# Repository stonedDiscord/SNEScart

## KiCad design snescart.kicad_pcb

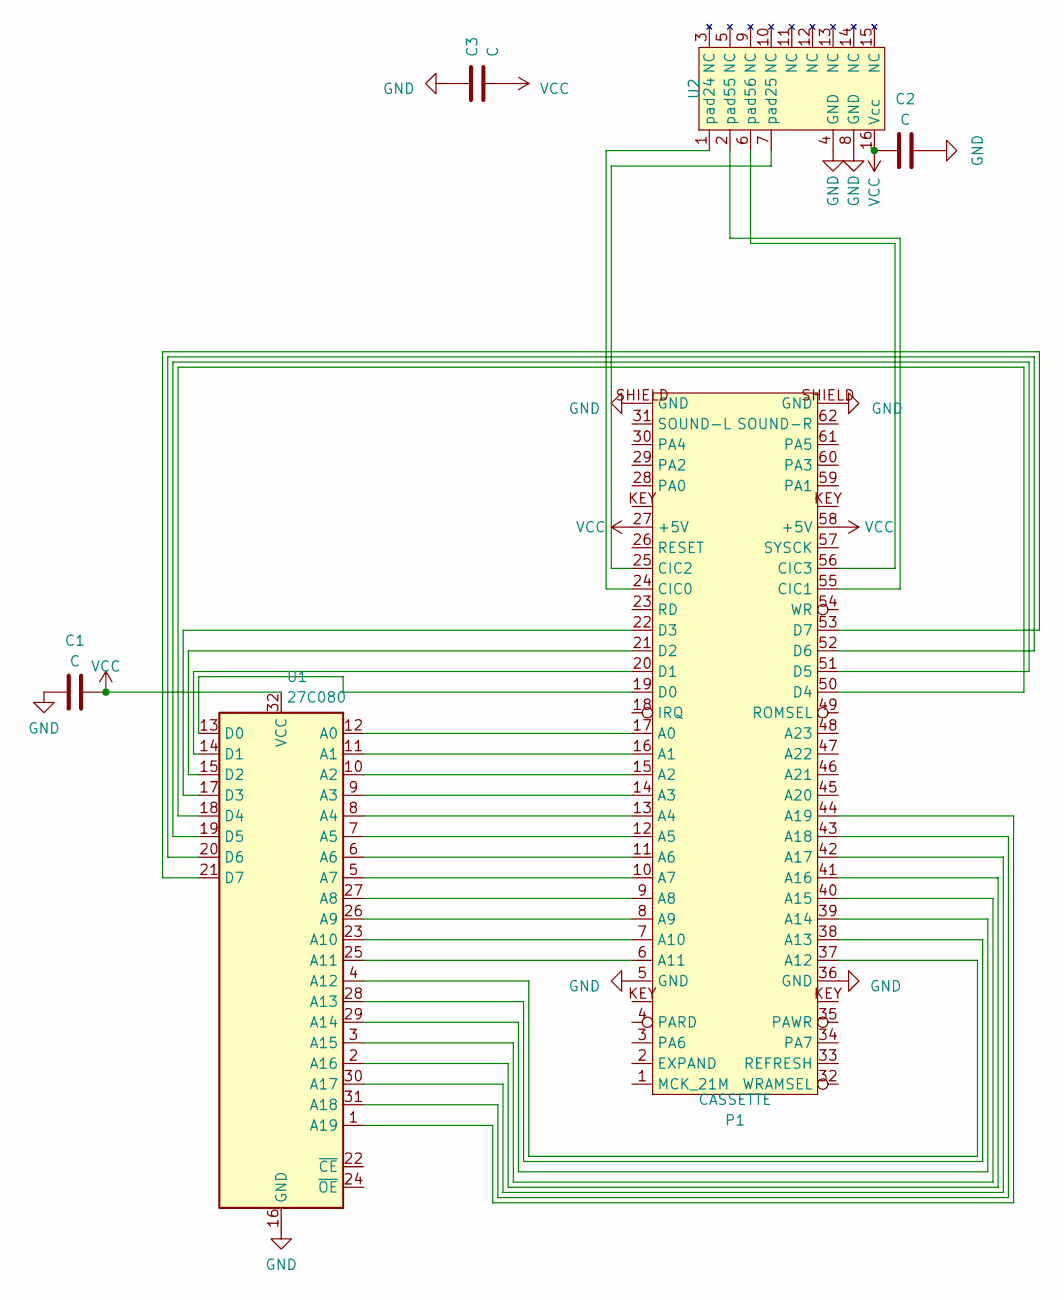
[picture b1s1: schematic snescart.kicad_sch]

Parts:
C1: C; CapacitorSpecial
C2, C3: C; Capacitor
P1: CASSETTE; CartEdge
U1: 27C080; DIP-32_W15.24mm
U2: DIP-16_W7.62mm

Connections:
GND: C1.1, C2.1, C3.1, P1.5 (GND), P1.36 (GND), P1.SHIELD (GND), U1.16 (GND), U2.4 (GND), U2.8 (GND)
unnamed: P1.17 (A0), U1.12 (A0)
unnamed: P1.16 (A1), U1.11 (A1)
unnamed: P1.15 (A2), U1.10 (A2)
unnamed: P1.14 (A3), U1.9 (A3)
unnamed: P1.13 (A4), U1.8 (A4)
unnamed: P1.12 (A5), U1.7 (A5)
unnamed: P1.11 (A6), U1.6 (A6)
unnamed: P1.10 (A7), U1.5 (A7)
unnamed: P1.9 (A8), U1.27 (A8)
unnamed: P1.8 (A9), U1.26 (A9)
unnamed: P1.7 (A10), U1.23 (A10)
unnamed: P1.6 (A11), U1.25 (A11)
unnamed: P1.37 (A12), U1.4 (A12)
unnamed: P1.38 (A13), U1.28 (A13)
unnamed: P1.39 (A14), U1.29 (A14)
unnamed: P1.40 (A15), U1.3 (A15)
unnamed: P1.41 (A16), U1.2 (A16)
unnamed: P1.42 (A17), U1.30 (A17)
unnamed: P1.43 (A18), U1.31 (A18)
unnamed: P1.44 (A19), U1.1 (A19)
unnamed: P1.24 (CIC0), U2.1 (pad24)
unnamed: P1.55 (CIC1), U2.2 (pad55)
unnamed: P1.25 (CIC2), U2.7 (pad25)
unnamed: P1.56 (CIC3), U2.6 (pad56)
unnamed: P1.19 (D0), U1.13 (D0)
unnamed: P1.20 (D1), U1.14 (D1)
unnamed: P1.21 (D2), U1.15 (D2)
unnamed: P1.22 (D3), U1.17 (D3)
unnamed: P1.50 (D4), U1.18 (D4)
unnamed: P1.51 (D5), U1.19 (D5)
unnamed: P1.52 (D6), U1.20 (D6)
unnamed: P1.53 (D7), U1.21 (D7)
VCC: C1.2, C2.2, C3.2, P1.27 (+5V), P1.58 (+5V), U1.32 (VCC), U2.16 (Vcc)

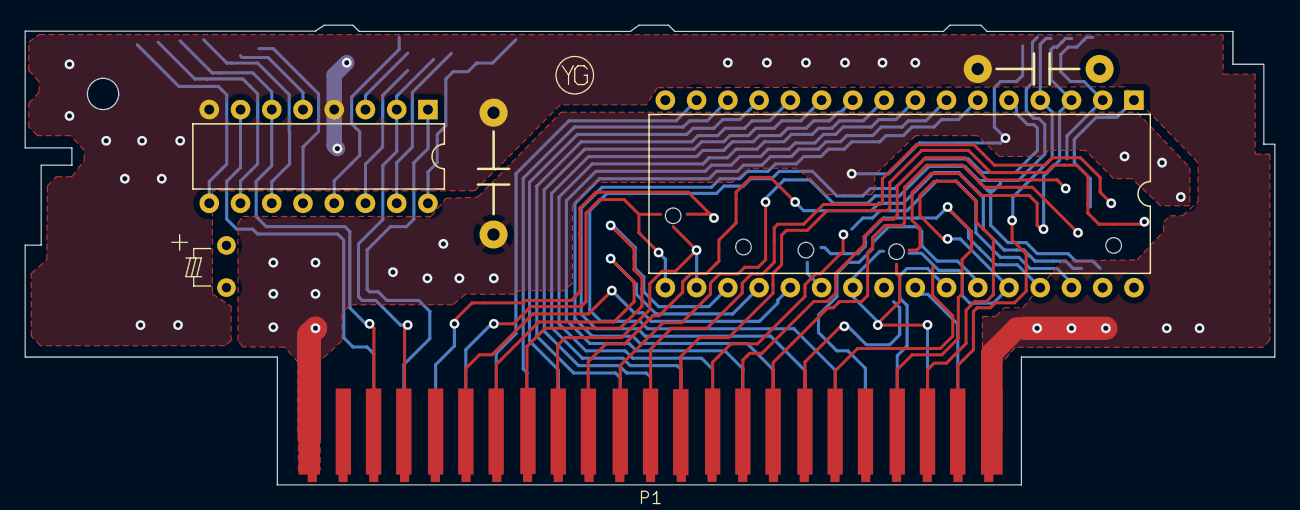
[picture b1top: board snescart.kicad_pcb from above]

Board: 2 copper layers, 101.6 x 37.4 mm, 6 parts (0 on the bottom side), 34 nets.

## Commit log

2023-07-26 this is wrong
2023-07-26 kibot files
2023-07-26 adjust colors
2023-07-26 fix img size
2023-07-26 fix cic
2023-07-26 update footprint
2023-07-26 feet
2023-07-26 forgot to acutally update the footprint in pcbnew
2023-07-26 more pins
2023-07-26 outline was messed up because of the size change
2023-07-26 edge
2023-07-26 connector
2023-07-26 0.5mm
2023-07-26 add little funny things
2023-07-26 cart
2023-07-26 tracks
2023-07-26 abababa
2023-07-26 track
2023-07-26 funny cap
2023-07-26 date
2023-07-26 jkfjf
2023-07-26 asdjus
2023-07-26 edfhgdfhg
2023-08-01 track and bottom
2023-08-01 fghrhsdrte
2023-08-01 holes
2023-08-01 bbbbb
2023-08-01 i cant draw
2023-08-02 specialcap
2023-08-02 font sizes
2023-08-03 vcc area
2023-08-03 bottom vcc
2023-08-03 what a mess
2023-08-03 clad color
2023-08-03 the cic is lower than the rom
2023-08-03 advanced movement
2023-08-03 more gimp work
2023-08-03 new photo
2023-08-03 next render
2023-08-03 imperial mil cart edge
2023-08-03 footprint again
2023-08-03 move edge
2023-08-03 38mil spacing smh
2023-08-03 aaaaaaa
2023-08-03 expand
2023-08-03 power trace was gone again
2023-08-03 bottom side got some love
2023-08-03 lotta traces
2023-08-03 ssssssss
2023-08-03 move cart edge AGAIN
2023-08-03 get rid of the card edge until i figure it out
2023-08-04 redo
2023-08-04 finally?
2023-08-04 rrrrrrip
2023-08-04 track club
2023-08-07 back was messed up
2023-08-21 ftghjdrftgh
2023-08-21 sdgs
2023-08-21 backss
2023-08-21 fix board outline
2023-08-25 swap cic pins
2023-08-31 triangle
2023-09-01 bo om gear
